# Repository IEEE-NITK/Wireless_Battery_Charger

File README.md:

# Wireless_Battery_Charger
The code and the KiCAD files have been added to this repository. The KiCAD files have been added as a rar file.

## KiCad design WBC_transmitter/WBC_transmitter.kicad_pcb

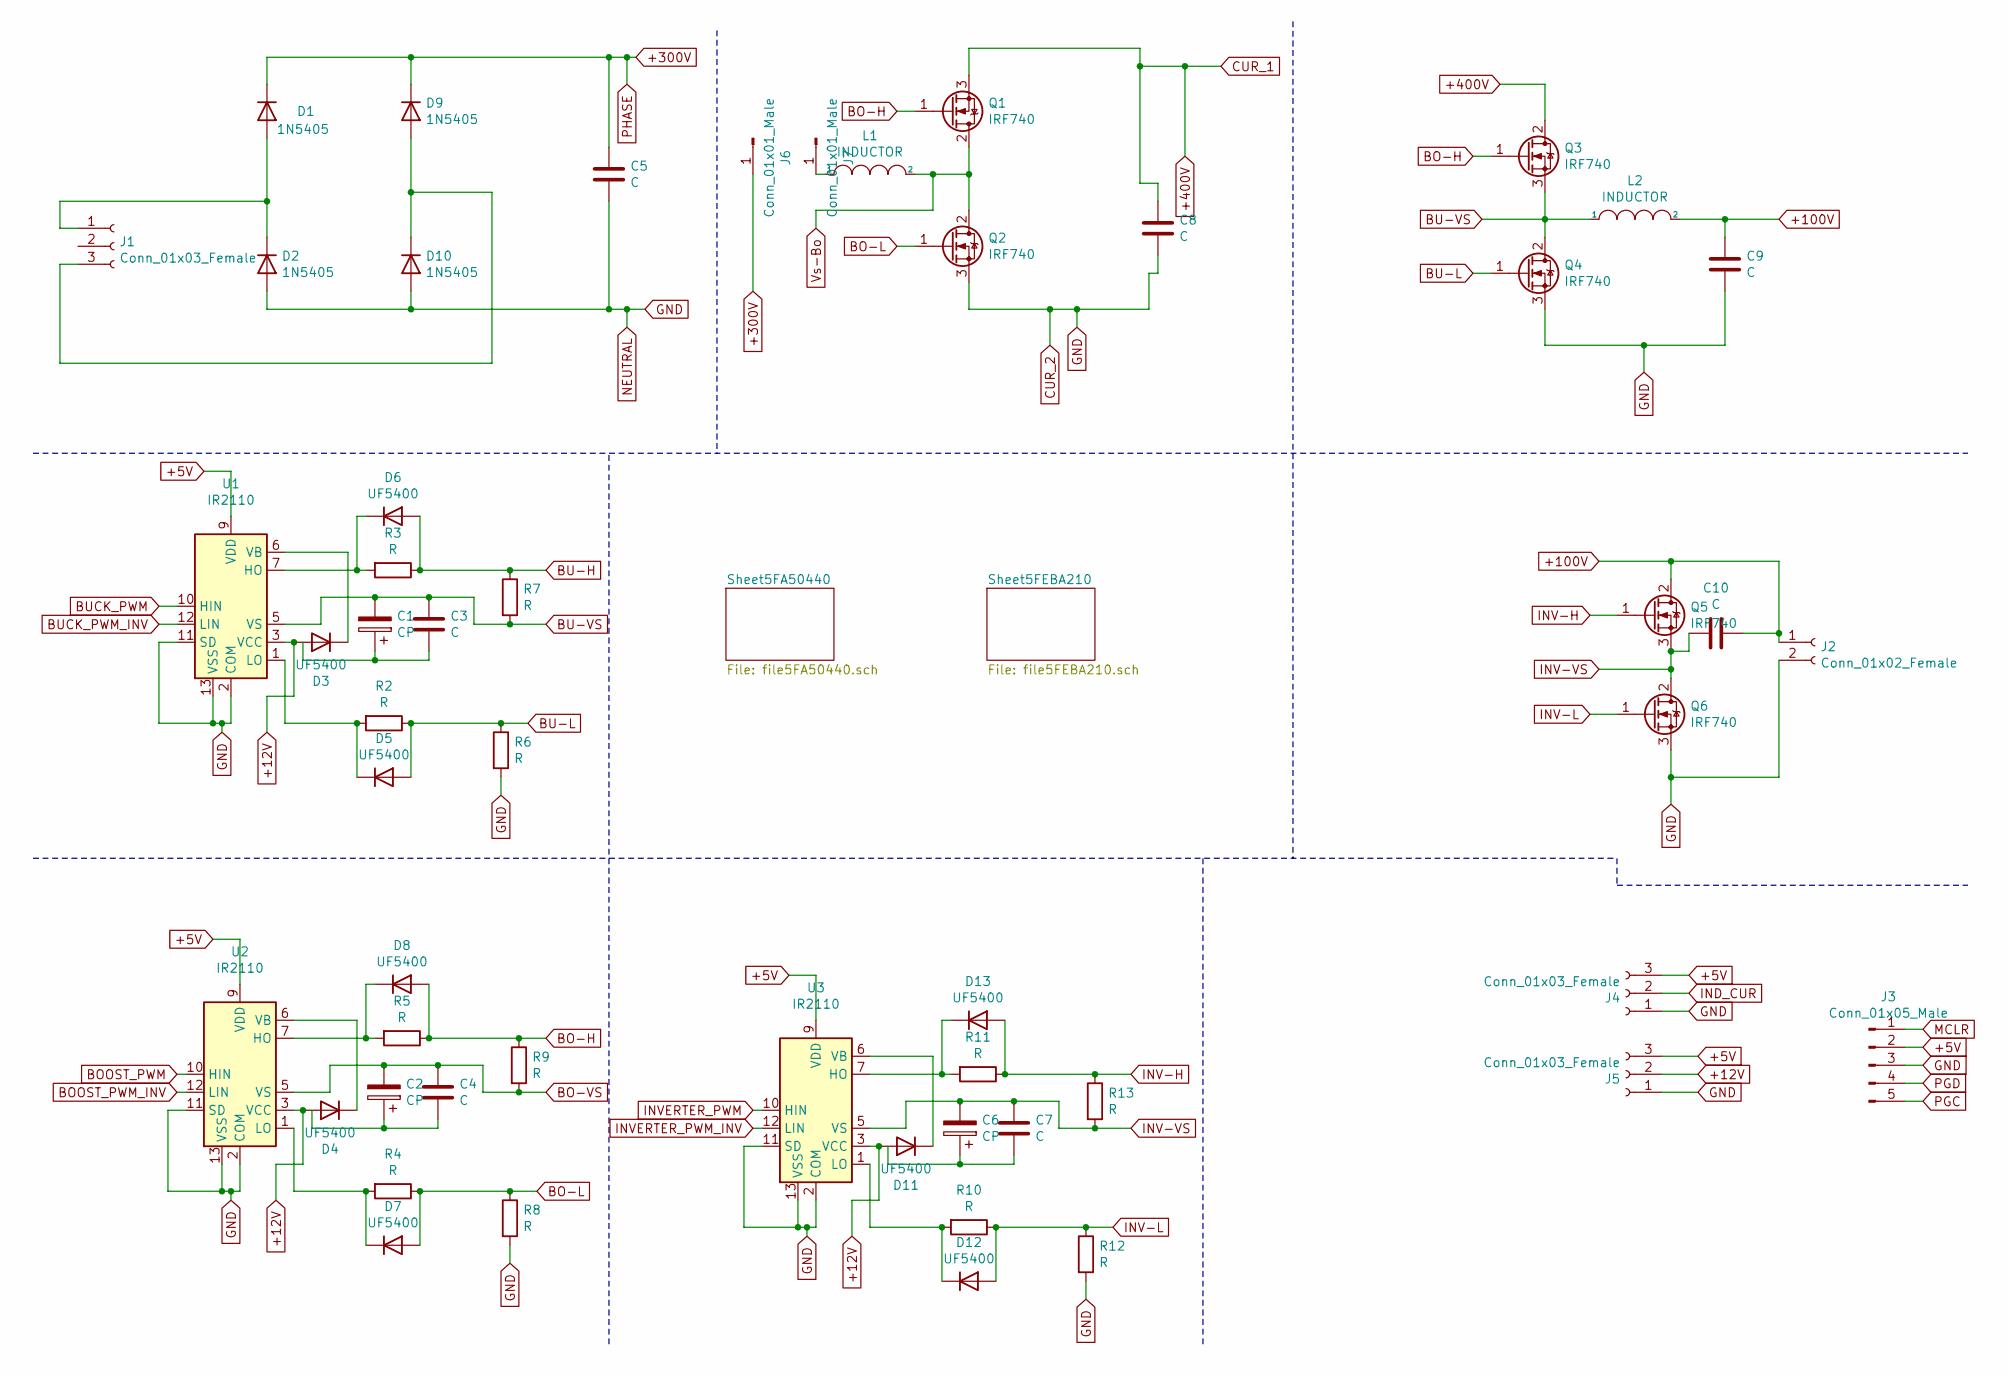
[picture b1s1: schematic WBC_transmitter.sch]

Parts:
C1, C2, C6: CP; CP_Radial_D5.0mm_P2.00mm
C3, C4, C5, C7, C8, C9, C10: C; C_Disc_D9.0mm_W2.5mm_P5.00mm
D1, D2, D9, D10: 1N5405; D_DO-201AD_P15.24mm_Horizontal
D3, D4, D5, D6, D7, D8, D11, D12, D13: UF5400; D_DO-201AD_P15.24mm_Horizontal
J1: Conn_01x03_Female; JST_NV_B03P-NV_1x03_P5.00mm_Vertical
J2: Conn_01x02_Female; JST_EH_B2B-EH-A_1x02_P2.50mm_Vertical
J3: Conn_01x05_Male; PinHeader_1x05_P2.54mm_Vertical
J4, J5: Conn_01x03_Female; PinHeader_1x03_P2.54mm_Vertical
J6, J7: Conn_01x01_Male; PinHeader_1x01_P2.54mm_Vertical
L1, L2: INDUCTOR; JST_EH_B2B-EH-A_1x02_P2.50mm_Vertical
Q1, Q2, Q3, Q4, Q5, Q6: IRF740; TO-220-3_Vertical
R2, R3, R4, R5, R6, R7, R8, R9, R10, R11, R12, R13: R; R_Axial_DIN0207_L6.3mm_D2.5mm_P10.16mm_Horizontal
U1, U2, U3: IR2110; DIP-14_W7.62mm

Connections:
+5V: J3.2, J4.3, J5.3, U1.9 (VDD), U2.9 (VDD), U3.9 (VDD); also elsewhere on the board
+12V: D3.2 (A), D4.2 (A), D11.2 (A), J5.2, U1.3 (VCC), U2.3 (VCC), U3.3 (VCC)
+100V: C9.1, C10.1, J2.1, L2.2, Q5.2 (D)
+300V: C5.1, D1.1 (K), D9.1 (K), J6.1; also elsewhere on the board
+400V: C8.1, Q1.3 (S), Q3.2 (D); also elsewhere on the board
BO-H: D8.2 (A), Q1.1 (G), Q3.1 (G), R5.1, R9.1
BO-L: D7.2 (A), Q2.1 (G), R4.1, R8.1
BO-VS: C2.2, C4.1, R9.2, U2.5 (VS)
BOOST_PWM: U2.10 (HIN); also elsewhere on the board
BOOST_PWM_INV: U2.12 (LIN); also elsewhere on the board
BU-H: D6.2 (A), R3.1, R7.1
BU-L: D5.2 (A), Q4.1 (G), R2.1, R6.1
BU-VS: C1.2, C3.1, L2.1, Q3.3 (S), Q4.2 (D), R7.2, U1.5 (VS)
BUCK_PWM: U1.10 (HIN); also elsewhere on the board
BUCK_PWM_INV: U1.12 (LIN); also elsewhere on the board
CUR_2: C5.2, C8.2, C9.2, D2.2 (A), D10.2 (A), J2.2, J3.3, J4.1, J5.1, Q2.3 (S), Q4.3 (S), Q6.3 (S), R6.2, R8.2, R12.2, U1.2 (COM), U1.11 (SD), U1.13 (VSS), U2.2 (COM), U2.11 (SD), U2.13 (VSS), U3.2 (COM), U3.11 (SD), U3.13 (VSS); also elsewhere on the board
IND_CUR: J4.2; also elsewhere on the board
INV-H: D13.2 (A), Q5.1 (G), R11.1, R13.1
INV-L: D12.2 (A), Q6.1 (G), R10.1, R12.1
INV-VS: C6.2, C7.1, C10.2, Q5.3 (S), Q6.2 (D), R13.2, U3.5 (VS)
INVERTER_PWM: U3.10 (HIN); also elsewhere on the board
INVERTER_PWM_INV: U3.12 (LIN); also elsewhere on the board
MCLR: J3.1; also elsewhere on the board
unnamed: C1.1, C3.2
unnamed: C2.1, C4.2
unnamed: C6.1, C7.2
unnamed: D1.2 (A), D2.1 (K), J1.1
unnamed: D3.1 (K), U1.6 (VB)
unnamed: D4.1 (K), U2.6 (VB)
unnamed: D5.1 (K), R2.2, U1.1 (LO)
unnamed: D6.1 (K), R3.2, U1.7 (HO)
unnamed: D7.1 (K), R4.2, U2.1 (LO)
unnamed: D8.1 (K), R5.2, U2.7 (HO)
unnamed: D9.2 (A), D10.1 (K), J1.3
unnamed: D11.1 (K), U3.6 (VB)
unnamed: D12.1 (K), R10.2, U3.1 (LO)
unnamed: D13.1 (K), R11.2, U3.7 (HO)
unnamed: J7.1, L1.1
PGC: J3.5; also elsewhere on the board
PGD: J3.4; also elsewhere on the board
Vs-Bo: L1.2, Q1.2 (D), Q2.2 (D)

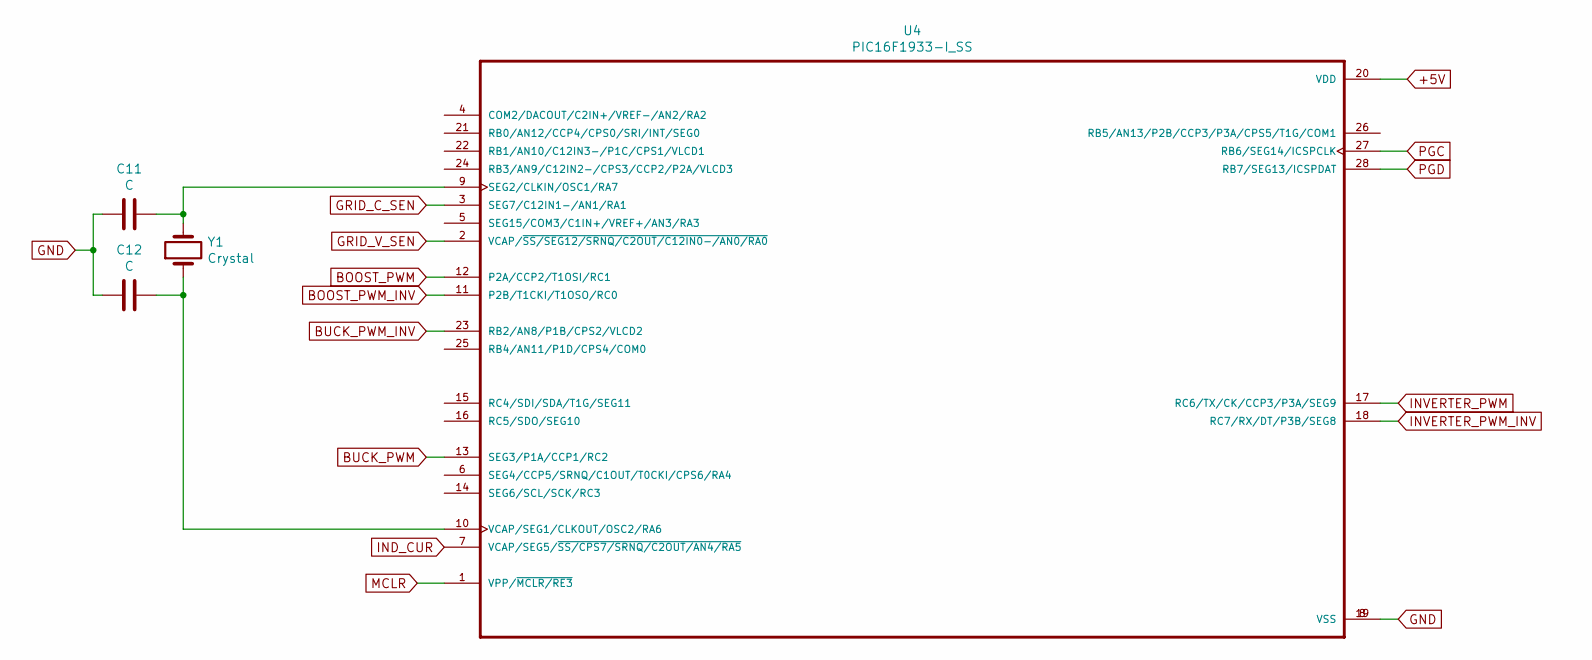
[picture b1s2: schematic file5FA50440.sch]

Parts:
C11, C12: C; C_Disc_D9.0mm_W2.5mm_P5.00mm
U4: PIC16F1933-I_SS; SOP65P780X200-28N
Y1: Crystal; R_Axial_DIN0411_L9.9mm_D3.6mm_P5.08mm_Vertical

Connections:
+5V: U4.20 (VDD); also elsewhere on the board
BOOST_PWM: U4.12 (P2A/CCP2/T1OSI/RC1); also elsewhere on the board
BOOST_PWM_INV: U4.11 (P2B/T1CKI/T1OSO/RC0); also elsewhere on the board
BUCK_PWM: U4.13 (SEG3/P1A/CCP1/RC2); also elsewhere on the board
BUCK_PWM_INV: U4.23 (RB2/AN8/P1B/CPS2/VLCD2); also elsewhere on the board
CUR_2: C11.2, C12.2, U4.8 (VSS), U4.19 (VSS); also elsewhere on the board
GRID_C_SEN: U4.3 (SEG7/C12IN1-/AN1/RA1); also elsewhere on the board
GRID_V_SEN: U4.2 (VCAP/~SS/SEG12/SRNQ/C2OUT/C12IN0-/AN0/R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); also elsewhere on the board
IND_CUR: U4.7 (VCAP/SEG5/~SS/CPS7/SRNQ/C2OUT/AN4/RA5); also elsewhere on the board
INVERTER_PWM: U4.17 (RC6/TX/CK/CCP3/P3A/SEG9); also elsewhere on the board
INVERTER_PWM_INV: U4.18 (RC7/RX/DT/P3B/SEG8); also elsewhere on the board
MCLR: U4.1 (VPP/~MCLR/RE3); also elsewhere on the board
unnamed: C11.1, U4.9 (SEG2/CLKIN/OSC1/RA7), Y1.2
unnamed: C12.1, U4.10 (VCAP/SEG1/CLKOUT/OSC2/RA6), Y1.1
PGC: U4.27 (RB6/SEG14/ICSPCLK); also elsewhere on the board
PGD: U4.28 (RB7/SEG13/ICSPDAT); also elsewhere on the board

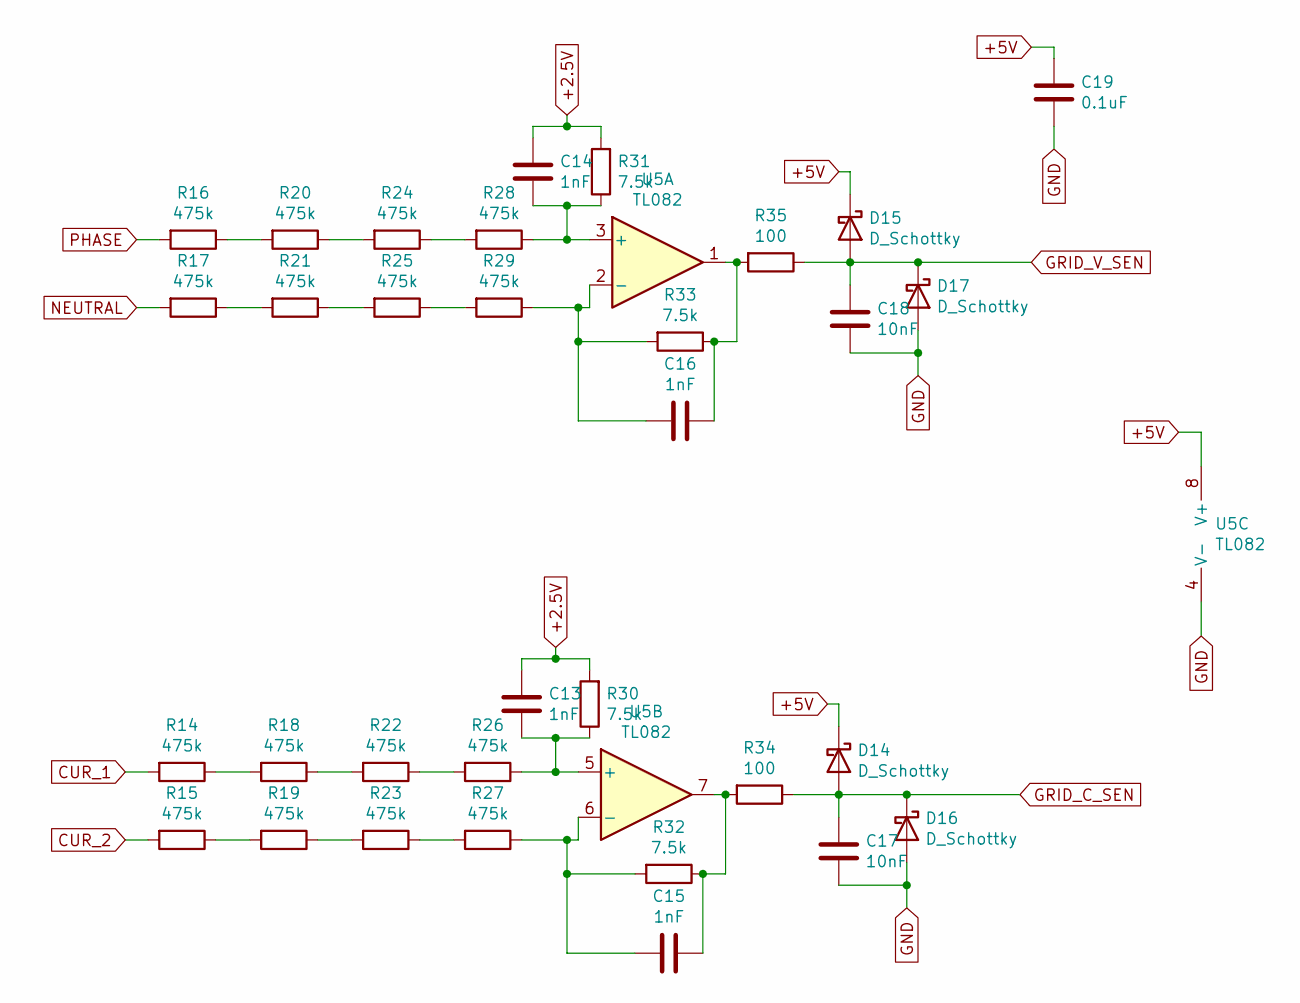
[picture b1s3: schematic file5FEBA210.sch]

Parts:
C13, C14, C15, C16: 1nF; C_Disc_D9.0mm_W2.5mm_P5.00mm
C17, C18: 10nF; C_Disc_D9.0mm_W2.5mm_P5.00mm
C19: 0.1uF; C_Disc_D9.0mm_W2.5mm_P5.00mm
D14, D15, D16, D17: D_Schottky; D_DO-41_SOD81_P10.16mm_Horizontal
R14, R15, R16, R17, R18, R19, R20, R21, R22, R23, R24, R25, R26, R27, R28, R29: 475k; R_0805_2012Metric_Pad1.20x1.40mm_HandSolder
R30, R31, R32, R33: 7.5k; R_0805_2012Metric_Pad1.20x1.40mm_HandSolder
R34, R35: 100; R_0805_2012Metric_Pad1.20x1.40mm_HandSolder
U5: TL082; DIP-8_W7.62mm

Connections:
+2.5V: C13.1, C14.1, R30.2, R31.2
+5V: C19.1, D14.1 (K), D15.1 (K), U5.8 (V+); also elsewhere on the board
+300V: R16.2; also elsewhere on the board
+400V: R14.2; also elsewhere on the board
CUR_2: C17.2, C18.2, C19.2, D16.2 (A), D17.2 (A), R15.2, R17.2, U5.4 (V-); also elsewhere on the board
GRID_C_SEN: C17.1, D14.2 (A), D16.1 (K), R34.1; also elsewhere on the board
GRID_V_SEN: C18.1, D15.2 (A), D17.1 (K), R35.1; also elsewhere on the board
unnamed: C13.2, R26.1, R30.1, U5.5 (+)
unnamed: C14.2, R28.1, R31.1, U5.3 (+)
unnamed: C15.1, R32.1, R34.2, U5.7
unnamed: C15.2, R27.1, R32.2, U5.6 (-)
unnamed: C16.1, R33.1, R35.2, U5.1
unnamed: C16.2, R29.1, R33.2, U5.2 (-)
unnamed: R14.1, R18.2
unnamed: R15.1, R19.2
unnamed: R16.1, R20.2
unnamed: R17.1, R21.2
unnamed: R18.1, R22.2
unnamed: R19.1, R23.2
unnamed: R20.1, R24.2
unnamed: R21.1, R25.2
unnamed: R22.1, R26.2
unnamed: R23.1, R27.2
unnamed: R24.1, R28.2
unnamed: R25.1, R29.2

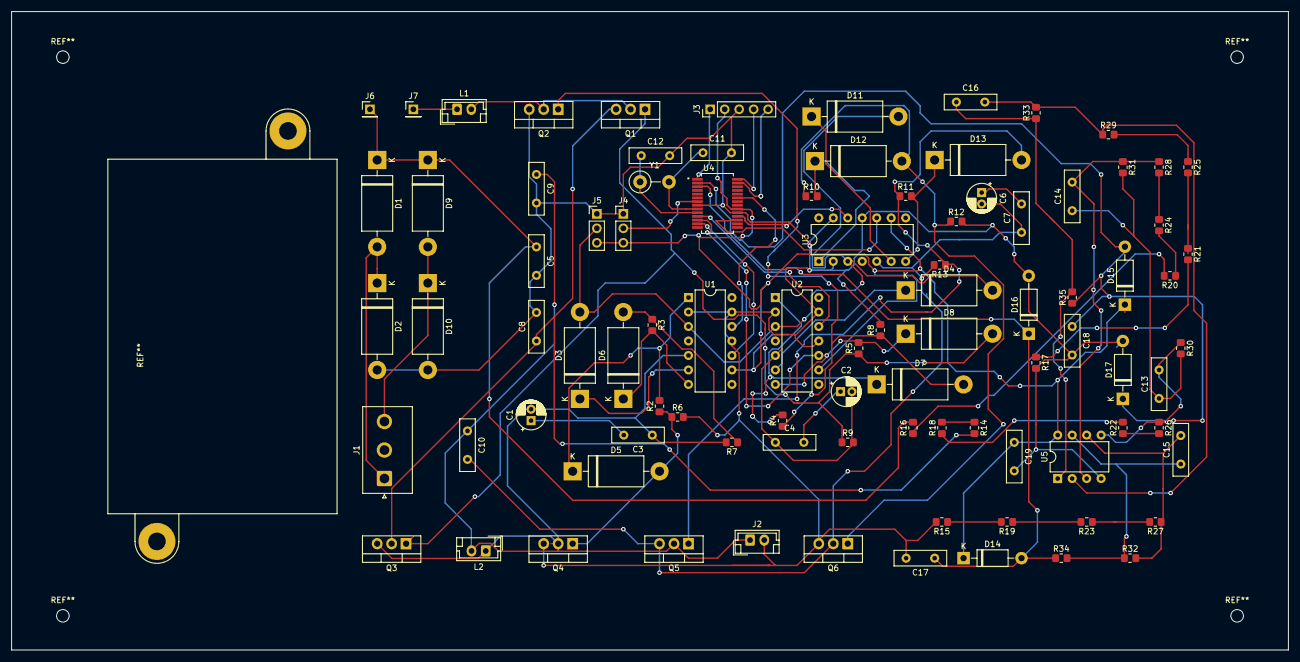
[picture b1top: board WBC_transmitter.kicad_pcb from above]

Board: 2 copper layers, 224.0 x 112.0 mm, 91 parts (0 on the bottom side), 64 nets.

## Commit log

2021-01-16 Started Routing
2021-01-16 Finished Placing
2021-01-19 Routing 80%
2021-01-23 24 unrouted
2021-02-01 Repo
2021-02-10 finished routing, have to remove unrouted paths
2021-02-10 3 unrouted
2021-02-10 Finished routing
2021-02-10 Finished routing unroutrd paths
2021-02-24 All paths routed
2021-03-08 Resistors changed and all paths routed
2021-03-09 Routing done
2021-04-05 Images
